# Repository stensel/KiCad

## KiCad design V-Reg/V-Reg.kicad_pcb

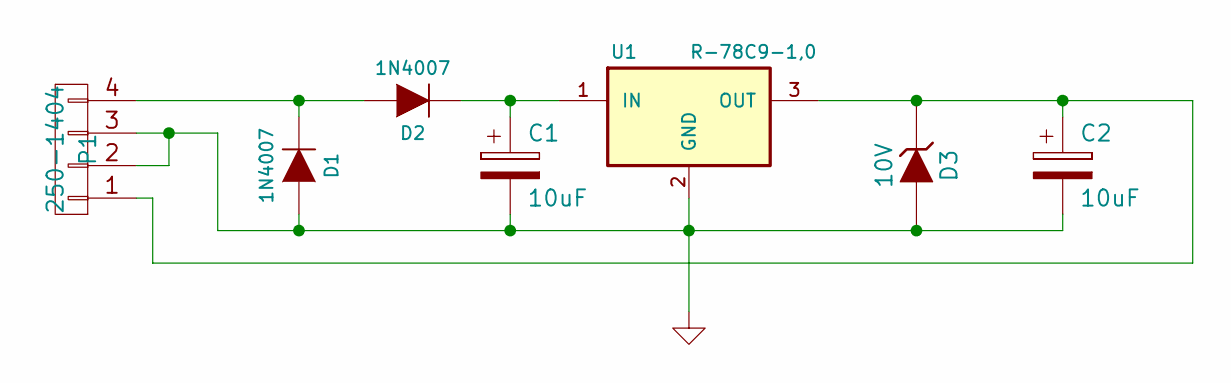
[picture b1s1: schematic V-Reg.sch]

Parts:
C1, C2: 10uF; C_Radial_D10_L20_P2.5
D1, D2: 1N4007; Diode_DO-35_SOD27_Horizontal_RM7,62
D3: 10V; Diode_DO-35_SOD27_Horizontal_RM7,62
P1: 250-1404; Wago_250-1404
U1: R-78C9-1,0; TO-220

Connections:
GND: C1.2, C2.2, D1.2 (A), D3.2 (A), P1.2, P1.3, U1.2 (GND)
unnamed: C1.1, D2.1 (K), U1.1 (IN)
unnamed: C2.1, D3.1 (K), P1.1, U1.3 (OUT)
unnamed: D1.1 (K), D2.2 (A), P1.4

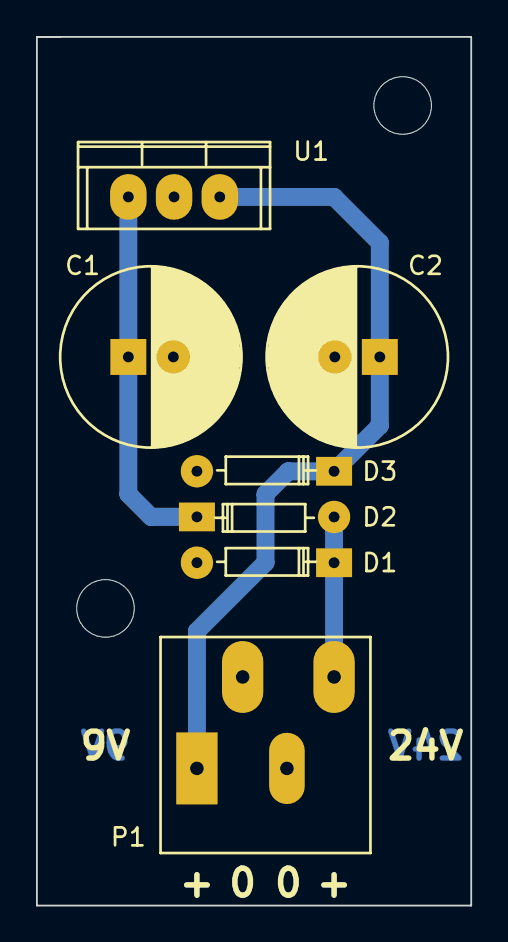
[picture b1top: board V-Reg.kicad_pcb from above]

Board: 2 copper layers, 24.1 x 48.3 mm, 7 parts (0 on the bottom side), 4 nets.

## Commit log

2016-03-11 Initial
